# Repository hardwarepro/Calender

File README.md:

# Calender
This is a custom-built calender PCB that allows me to upload my school schedule (or just counting down how many days of school I have left!) via WIFI (on an esp32) to an e-ink display and use it in my locker off a AA battery. When it's at home, it will be able to act as a music player or still a calender, allowing me to plug it in via usb-c or just by using wifi and display live music status.  

## Photos

## BOM

| Name | Part # | JLCPCB Part # | Qty | Total Price |
| :--- | :--- | :--- | :--- | :--- |
| 10uF | CL10A106KP8NNNC | C19702 | 20 | 0.112 |
| 4.7uF | CL10A475KO8NNNC | C19666 | 20 | 0.202 |
| 1uF | CL10A105KB8NNNC | C15849 | 20 | 0.094 |
| 100nF | CC0603KRX7R9BB104 | C14663 | 22 | 0.0506 |
| Conn_01x09 | ZX-PZ1.0-1-9PZZ | C37328859 | 2 | 0.2856 |
| USB_C_Receptacle_USB2.0_16P | GT-USB-7010ASV | C2988369 | 2 | 0.1572 |
| Power | DB128L-5.08-2P-GN-S | C395868 | 2 | 0.3622 |
| 5.1k | 0603WAF5101T5E | C23186 | 20 | 0.02 |
| 2k | 0603WAF2001T5E | C22975 | 20 | 0.02 |
| 10k | 0603WAF1002T5E | C25804 | 26 | 0.0234 |
| 100kΩ | 0603WAF1003T5E | C25803 | 20 | 0.02 |
| RotaryEncoder_Switch | EC11E18244AU | C202365 | 2 | 3.825 |
| SW_Push | BTSA-N-P-13 | C2693637 | 0 | 0 |
| ATSAMD21G18A-A | ATSAMD21G18A-AU | C78624 | 2 | 6.249 |
| MCP73871 | MCP73871T-2CCI/ML | C511310 | 2 | 7.482 |
| ESP-WROOM-02 | ESP-WROOM-02D-N4 | C529584 | 2 | 3.75 |
| AMS1117-3.3V | AMS1117-3.3V |  | 2 | 1.25 |
| PCB | | | $76.80 after tax + shipping ||

---

## Other Items

| Item | Details/Source | Qty | Price |
| :--- | :--- | :--- | :--- |
| 0.91 OLED | 0.91 OLED | 1 | $1.15 since mine just broke :( |
| E-Ink Display | [From Waveshare](https://www.waveshare.com/3.7inch-e-paper-hat-plus-g.htm?sku=31061) | 2 | $48.98 after tax + shipping |

---

### **TOTAL: $126.93 USD without customs**

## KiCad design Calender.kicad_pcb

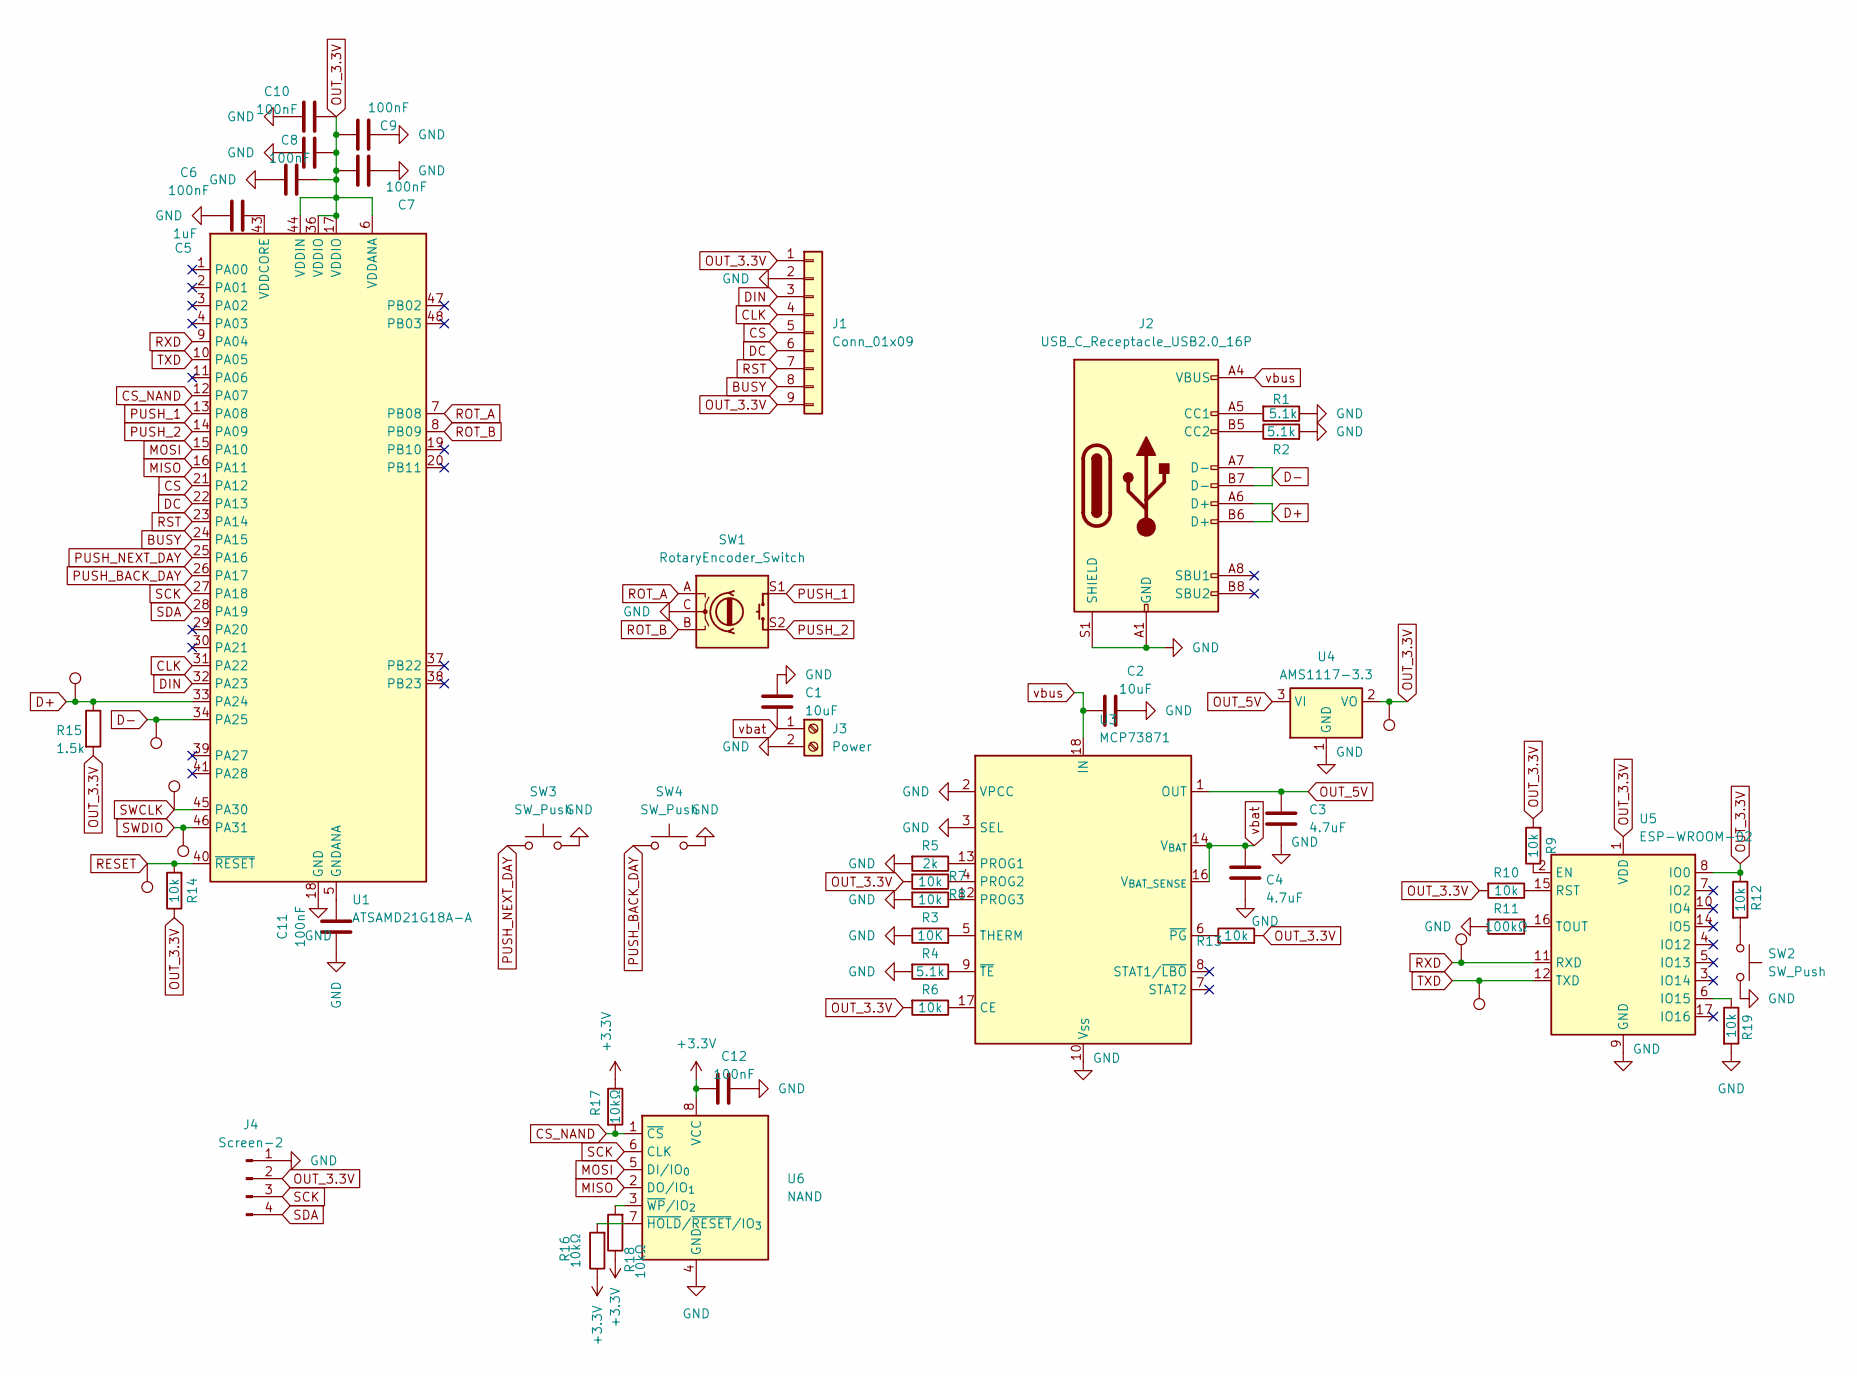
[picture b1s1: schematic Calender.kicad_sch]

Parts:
C1, C2: 10uF; C_0603_1608Metric
C3, C4: 4.7uF; C_0603_1608Metric
C5: 1uF; C_0603_1608Metric
C6, C7, C8, C9, C10, C11, C12: 100nF; C_0603_1608Metric
J1: Conn_01x09; PinHeader_1x09_P1.00mm_Vertical
J2: USB_C_Receptacle_USB2.0_16P; USB_C_Receptacle_HCTL_HC-TYPE-C-16P-01A
J3: Power; TerminalBlock_bornier-2_P5.08mm
J4: Screen-2; PinHeader_1x04_P2.54mm_Vertical
R1, R2, R4: 5.1k; R_0603_1608Metric
R3: 10K; R_0603_1608Metric
R5: 2k; R_0603_1608Metric
R6, R7, R8, R9, R10, R12, R13, R14, R19: 10k; R_0603_1608Metric
R11: 100kΩ; R_0603_1608Metric
R15: 1.5k; R_0603_1608Metric
R16, R17, R18: 10kΩ; R_0603_1608Metric
SW1: RotaryEncoder_Switch; RotaryEncoder_Alps_EC11E-Switch_Vertical_H20mm
SW2, SW3, SW4: SW_Push; SW_PUSH_6mm
TP1, TP2, TP3, TP4, TP5, TP6, TP7, TP8: TestPoint; Pin_D1.0mm_L10.0mm_LooseFit
U1: ATSAMD21G18A-A; TQFP-48_7x7mm_P0.5mm
U3: MCP73871; QFN-20-1EP_4x4mm_P0.5mm_EP2.5x2.5mm
U4: AMS1117-3.3; SOT-223-3_TabPin2
U5: ESP-WROOM-02
U6: NAND; SOIC-8_5.3x5.3mm_P1.27mm

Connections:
+3.3V: C12.1, R16.1, R17.1, R18.1, U6.8 (VCC)
BUSY: J1.8, U1.24 (PA15)
CLK: J1.4, U1.31 (PA22)
CS: J1.5, U1.21 (PA12)
CS_NAND: R17.2, U1.12 (PA07), U6.1 (~CS)
D+: J2.A6 (D+), J2.B6 (D+), R15.1, TP6.1, U1.33 (PA24)
D-: J2.A7 (D-), J2.B7 (D-), TP7.1, U1.34 (PA25)
DC: J1.6, U1.22 (PA13)
DIN: J1.3, U1.32 (PA23)
GND: C1.1, C2.2, C3.2, C4.2, C5.2, C6.2, C7.2, C8.2, C9.2, C10.2, C11.2, C12.2, J1.2, J2.A1 (GND), J2.A12 (GND), J2.B1 (GND), J2.B12 (GND), J2.S1 (SHIELD), J3.2, J4.1, R1.1, R2.2, R3.1, R4.2, R5.2, R8.2, R11.2, R19.2, SW1.C, SW2.2, SW3.2, SW4.2, U1.18 (GND), U1.35 (GND), U1.42 (GND), U3.2 (VPCC), U3.3 (SEL), U3.10 (V_{SS}), U3.11 (V_{SS}), U3.21 (V_{SS}), U4.1 (GND), U5.9 (GND), U5.13 (GND), U5.18 (GND), U5.19 (GND), U6.4 (GND)
MISO: U1.16 (PA11), U6.2 (DO/IO_{1})
MOSI: U1.15 (PA10), U6.5 (DI/IO_{0})
unnamed: J2.A5 (CC1), R1.2
unnamed: J2.B5 (CC2), R2.1
unnamed: R12.2, SW2.1
unnamed: C11.1, U1.5 (GNDANA)
unnamed: C5.1, U1.43 (VDDCORE)
unnamed: R6.1, U3.17 (CE)
unnamed: R5.1, U3.13 (PROG1)
unnamed: R7.1, U3.4 (PROG2)
unnamed: R8.1, U3.12 (PROG3)
unnamed: R3.2, U3.5 (THERM)
unnamed: R13.1, U3.6 (~PG)
unnamed: R4.1, U3.9 (~TE)
unnamed: R9.1, U5.2 (EN)
unnamed: R19.1, U5.6 (IO15)
unnamed: R10.1, U5.15 (RST)
unnamed: R11.1, U5.16 (TOUT)
unnamed: R16.2, U6.7 (~HOLD/~RESET/IO_{3})
unnamed: R18.2, U6.3 (~WP/IO_{2})
OUT_3.3V: C6.1, C7.1, C8.1, C9.1, C10.1, J1.1, J1.9, J4.2, R6.2, R7.2, R9.2, R10.2, R12.1, R13.2, R14.1, R15.2, TP8.1, U1.6 (VDDANA), U1.17 (VDDIO), U1.36 (VDDIO), U1.44 (VDDIN), U4.2 (VO), U5.1 (VDD), U5.8 (IO0)
OUT_5V: C3.1, U3.1 (OUT), U3.20 (OUT), U4.3 (VI)
PUSH_1: SW1.S1, U1.13 (PA08)
PUSH_2: SW1.S2, U1.14 (PA09)
PUSH_BACK_DAY: SW4.1, U1.26 (PA17)
PUSH_NEXT_DAY: SW3.1, U1.25 (PA16)
RESET: R14.2, TP3.1, U1.40 (~RESET)
ROT_A: SW1.A, U1.7 (PB08)
ROT_B: SW1.B, U1.8 (PB09)
RST: J1.7, U1.23 (PA14)
RXD: TP2.1, U1.9 (PA04), U5.11 (RXD)
SCK: J4.3, U1.27 (PA18), U6.6 (CLK)
SDA: J4.4, U1.28 (PA19)
SWCLK: TP5.1, U1.45 (PA30)
SWDIO: TP4.1, U1.46 (PA31)
TXD: TP1.1, U1.10 (PA05), U5.12 (TXD)
vbat: C1.2, C4.1, J3.1, U3.14 (V_{BAT}), U3.15 (V_{BAT}), U3.16 (V_{BAT_SENSE})
vbus: C2.1, J2.A4 (VBUS), J2.A9 (VBUS), J2.B4 (VBUS), J2.B9 (VBUS), U3.18 (IN), U3.19 (IN)

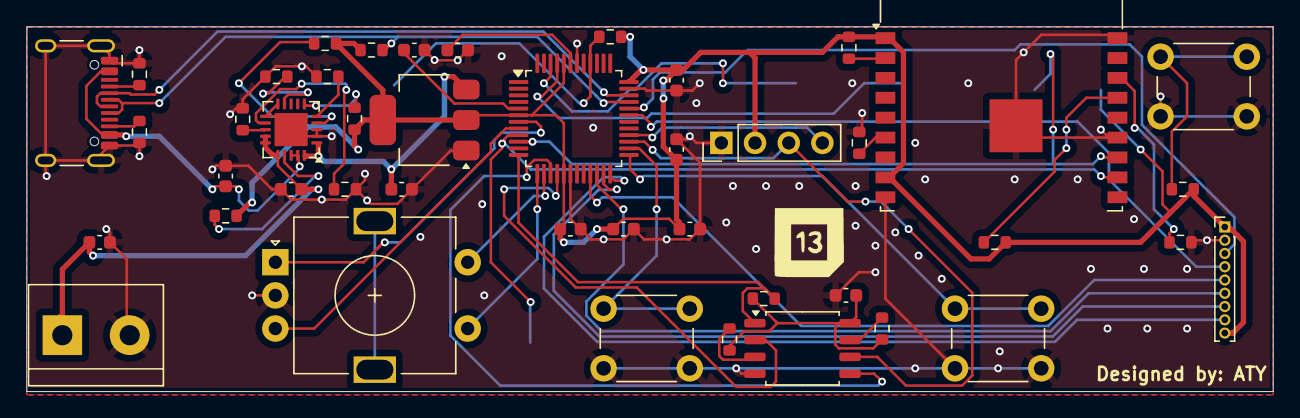
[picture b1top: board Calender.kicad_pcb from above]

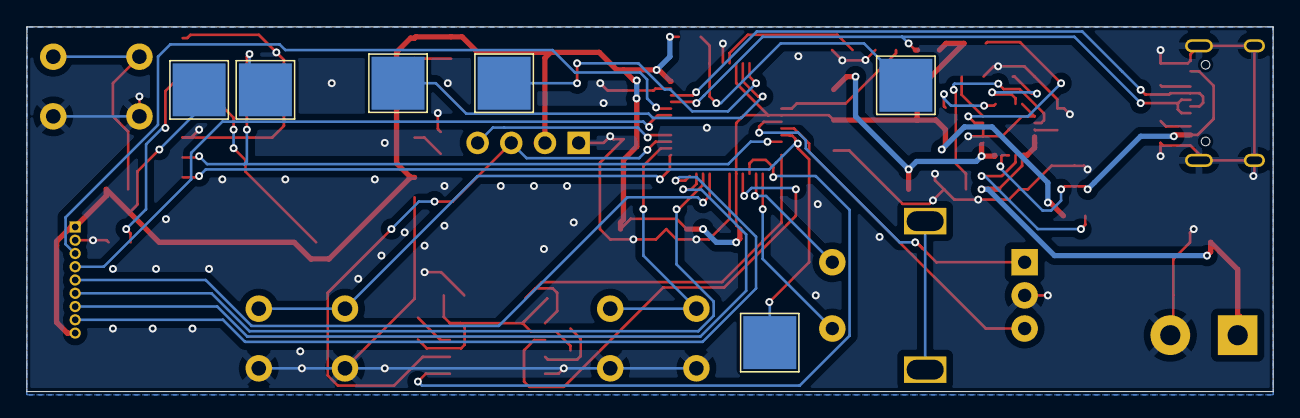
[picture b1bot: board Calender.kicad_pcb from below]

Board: 2 copper layers, 94.0 x 27.5 mm, 50 parts (6 on the bottom side), 48 nets.

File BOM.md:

| Name | Part # | JLCPCB Part # | Qty | Total Price |
| :--- | :--- | :--- | :--- | :--- |
| 10uF | CL10A106KP8NNNC | C19702 | 20 | 0.112 |
| 4.7uF | CL10A475KO8NNNC | C19666 | 20 | 0.202 |
| 1uF | CL10A105KB8NNNC | C15849 | 20 | 0.094 |
| 100nF | CC0603KRX7R9BB104 | C14663 | 22 | 0.0506 |
| Conn_01x09 | ZX-PZ1.0-1-9PZZ | C37328859 | 2 | 0.2856 |
| USB_C_Receptacle_USB2.0_16P | GT-USB-7010ASV | C2988369 | 2 | 0.1572 |
| Power | DB128L-5.08-2P-GN-S | C395868 | 2 | 0.3622 |
| 5.1k | 0603WAF5101T5E | C23186 | 20 | 0.02 |
| 2k | 0603WAF2001T5E | C22975 | 20 | 0.02 |
| 10k | 0603WAF1002T5E | C25804 | 26 | 0.0234 |
| 100kΩ | 0603WAF1003T5E | C25803 | 20 | 0.02 |
| RotaryEncoder_Switch | EC11E18244AU | C202365 | 2 | 3.825 |
| SW_Push | BTSA-N-P-13 | C2693637 | 0 | 0 |
| ATSAMD21G18A-A | ATSAMD21G18A-AU | C78624 | 2 | 6.249 |
| MCP73871 | MCP73871T-2CCI/ML | C511310 | 2 | 7.482 |
| ESP-WROOM-02 | ESP-WROOM-02D-N4 | C529584 | 2 | 3.75 |
| PCB | | | $71.70 after tax + shipping |

---

## Other Items

| Item | Details/Source | Qty | Price |
| :--- | :--- | :--- | :--- |
| AMS1117-3.3V (So I don't need to do 2 layer assembly. I will just hand-solder this myself)| From Digikey | 1 | $6.96 after tax + shipping |
| E-Ink Display | [From Waveshare](https://www.waveshare.com/3.7inch-e-paper-hat-plus-g.htm?sku=31061) | 1 | $26.99 after tax + $5 shipping |

---

### **TOTAL: $110 USD without customs**

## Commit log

2025-06-25 Finished the schematic
2025-07-08 all routing and stuff... definitely didn't forget to push
2025-07-08 Fixed via
2025-07-08 PCB finished
2025-07-09 Added BOM
2025-07-09 Added prod files and bootloader stuff
2025-07-27 The PCB should be good now for production
2025-07-28 Added step file
2025-07-28 forgot to push my code for the middleman stuff. Frontend can get finsihed eventaully
2025-07-29 Fixed PCB changes/errors
2025-07-30 Adding initial design for my case
2025-07-30 Fixed more small PCB changed. Everything should be good now.
2025-07-30 Added today's journal
2025-07-31 Update images
2025-07-31 added photos
2025-07-31 Added the pcb to the case
2025-08-18 have fun finishing the routing for it
2025-08-18 Should be finished
2025-08-18 Added production files
2025-08-18 added folder
2025-08-19 added the newest 3d model
